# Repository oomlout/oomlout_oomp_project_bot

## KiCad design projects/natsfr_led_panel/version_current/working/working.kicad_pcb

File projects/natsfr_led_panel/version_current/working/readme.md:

# OOMP Project  
## Led_Panel  by natsfr  
  
oomp key: oomp_projects_flat_natsfr_led_panel  
(snippet of original readme)  

  full source readme at [readme_src.md](readme_src.md)  
  
source repo at: [https://github.com/natsfr/Led_Panel](https://github.com/natsfr/Led_Panel)  
## Board  

## Schematic  

[schematic pdf](working_schematic.pdf)  
## Images

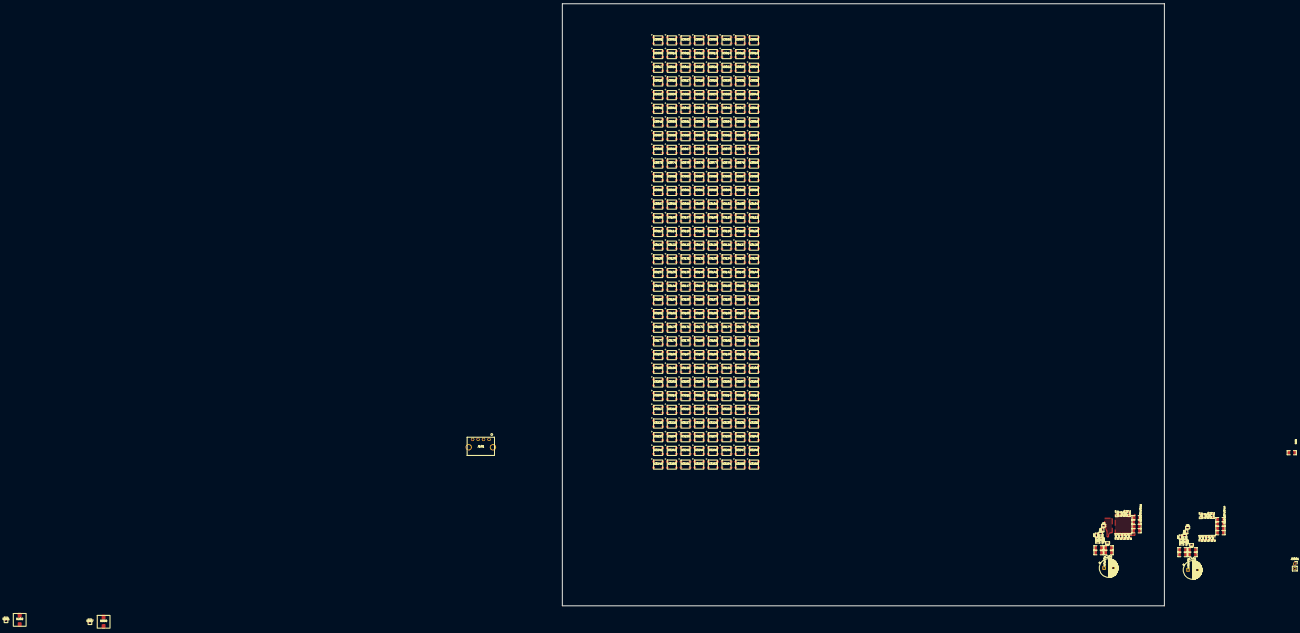
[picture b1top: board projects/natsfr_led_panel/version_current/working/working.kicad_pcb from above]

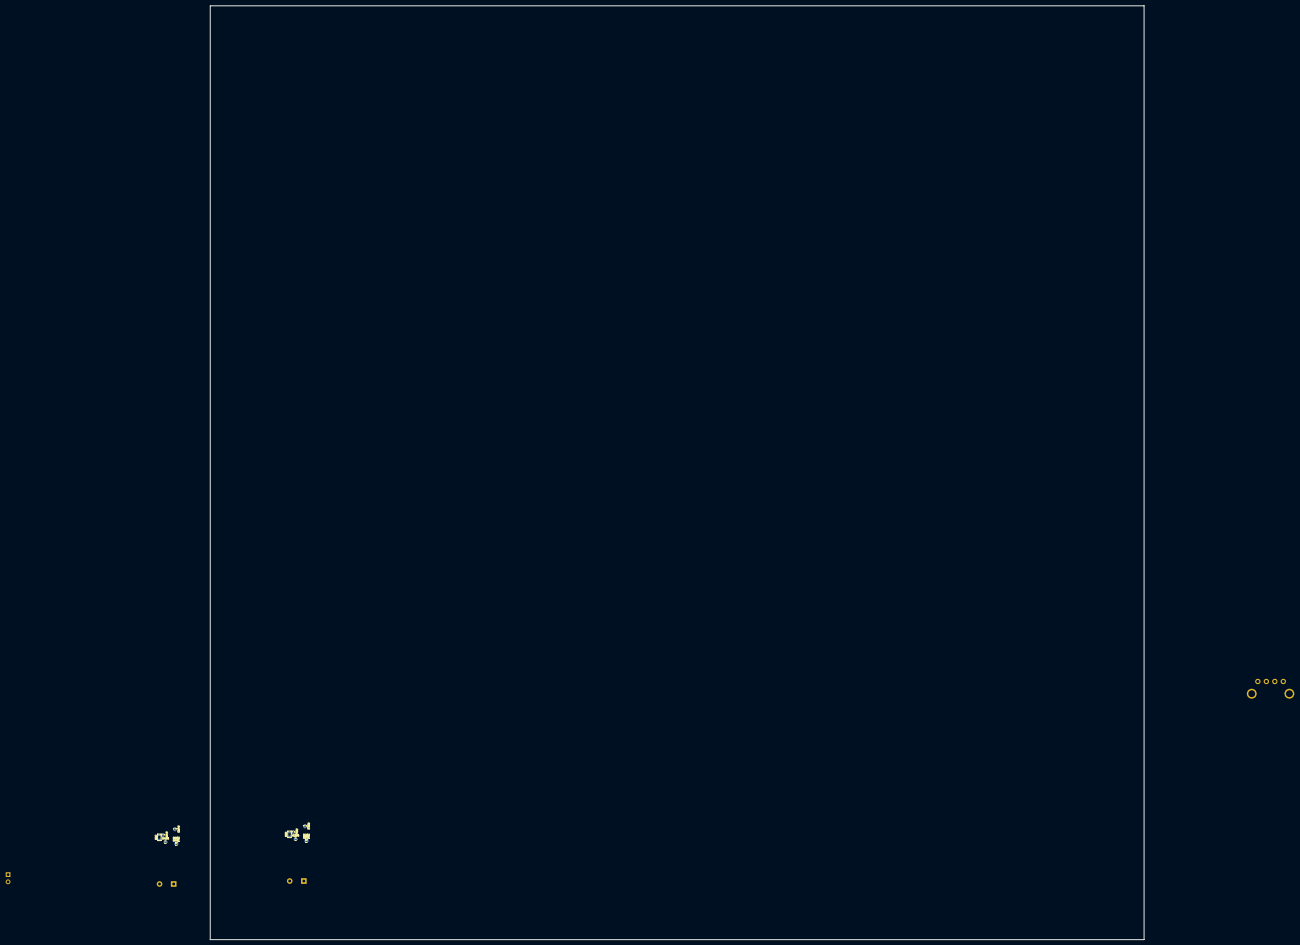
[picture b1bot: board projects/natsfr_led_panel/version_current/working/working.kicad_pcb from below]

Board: 4 copper layers, 330.0 x 330.0 mm, 331 parts (12 on the bottom side), 296 nets, no tracks yet.

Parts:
C201, C202, C203, C204, C402, C403, C404, C405: 10uF - 50V; SM1206
C205, C401: 100uF; CP_Radial_D10.0mm_P5.00mm
C206, C217, C218, C220, C406, C409, C419, C420: 100nF; SM0603
C207, C408: 220nF; SM0603
C208, C410: NC; SM0603
C209, C210, C211, C212, C213, C214, C215, C216, C411, C412, C413, C414, C415, C416, C417, C418: 10uF - 16V; SM0805
C219, C407: 1uF; SM0603
J101: 19V 5A Molex; MICROFIT_4POS_FEM_43650-0404
J3001: DEBUG_OUT; PinSocket_1x02_P2.54mm_Vertical
R101: RES_1206; SM1206
R201, R401: 1.5M; SM0402
R202, R212, R213, R402, R403, R404: NC; SM0402
R203, R409: 9.53k; SM0402
R204, R410: 43k; SM0402
R205, R405: 3.3; SM0603
R206, R207, R407, R408: NC; SM0603
R208, R209, R210, R211, R411, R412, R413, R414: 0; SM1206
R214, R406: 100k; SM0402
U201, U557: MP8759GD; MP8759_QFN12
U202, U558: IND_SMALL; WE-HCI_7x7x3.8mm
U3001, U3002, U3003, U3004, U3005, U3006, U3007, U3008, U3009, U3010, U3011, U3012, U3013, U3014, U3015, U3016, U3017, U3018, U3019, U3020, U3021, U3022, U3023, U3024, U3025, U3026, U3027, U3028, U3029, U3030, U3031, U3032, U3033, U3034, U3035, U3036, U3037, U3038, U3039, U3040, U3041, U3042, U3043, U3044, U3045, U3046, U3047, U3048, U3049, U3050, U3051, U3052, U3053, U3054, U3055, U3056, U3057, U3058, U3059, U3060, U3061, U3062, U3063, U3064, U3065, U3066, U3067, U3068, U3069, U3070, U3071, U3072, U3073, U3074, U3075, U3076, U3077, U3078, U3079, U3080, U3081, U3082, U3083, U3084, U3085, U3086, U3087, U3088, U3089, U3090, U3091, U3092, U3093, U3094, U3095, U3096, U3097, U3098, U3099, U3100, U3101, U3102, U3103, U3104, U3105, U3106, U3107, U3108, U3109, U3110, U3111, U3112, U3113, U3114, U3115, U3116, U3117, U3118, U3119, U3120, U3121, U3122, U3123, U3124, U3125, U3126, U3127, U3128, U3129, U3130, U3131, U3132, U3133, U3134, U3135, U3136, U3137, U3138, U3139, U3140, U3141, U3142, U3143, U3144, U3145, U3146, U3147, U3148, U3149, U3150, U3151, U3152, U3153, U3154, U3155, U3156, U3157, U3158, U3159, U3160, U3161, U3162, U3163, U3164, U3165, U3166, U3167, U3168, U3169, U3170, U3171, U3172, U3173, U3174, U3175, U3176, U3177, U3178, U3179, U3180, U3181, U3182, U3183, U3184, U3185, U3186, U3187, U3188, U3189, U3190, U3191, U3192, U3193, U3194, U3195, U3196, U3197, U3198, U3199, U3200, U3201, U3202, U3203, U3204, U3205, U3206, U3207, U3208, U3209, U3210, U3211, U3212, U3213, U3214, U3215, U3216, U3217, U3218, U3219, U3220, U3221, U3222, U3223, U3224, U3225, U3226, U3227, U3228, U3229, U3230, U3231, U3232, U3233, U3234, U3235, U3236, U3237, U3238, U3239, U3240, U3241, U3242, U3243, U3244, U3245, U3246, U3247, U3248, U3249, U3250, U3251, U3252, U3253, U3254, U3255, U3256: WS2812B; WS2812B_50x50

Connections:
/Lane 0/LANE_POWER: R101.2, U3001.1 (VDD), U3002.1 (VDD), U3003.1 (VDD), U3004.1 (VDD), U3005.1 (VDD), U3006.1 (VDD), U3007.1 (VDD), U3008.1 (VDD), U3009.1 (VDD), U3010.1 (VDD), U3011.1 (VDD), U3012.1 (VDD), U3013.1 (VDD), U3014.1 (VDD), U3015.1 (VDD), U3016.1 (VDD)
/Power Lane 0/19V: C201.2, C202.2, C203.2, C204.2, C205.2, C206.2, C401.2, C402.2, C403.2, C404.2, C405.2, C406.2, J101.3, J101.4, U201.1 (Vin), U557.1 (Vin)
/Power Lane 0/PG: R214.2, U201.3 (PG)
/Power Lane 0/POUT_SW: C208.2, C209.2, C210.2, C211.2, C212.2, C213.2, C214.2, C215.2, C216.2, C217.2, C218.2, C220.2, R204.1, R208.1, R209.1, R210.1, R211.1, U201.5 (Vout), U202.2
/Power Lane 0/POWER_OUT: R101.1, R208.2, R209.2, R210.2, R211.2
/Power Lane 0/SW: C207.2, R206.2, U201.7 (SW), U202.1
/Power Lane 1/PG: R406.2, U557.3 (PG)
/Power Lane 1/POUT_SW: C409.2, C410.2, C411.2, C412.2, C413.2, C414.2, C415.2, C416.2, C417.2, C418.2, C419.2, C420.2, R410.1, R411.1, R412.1, R413.1, R414.1, U557.5 (Vout), U558.2
/Power Lane 1/POWER_OUT: R411.2, R412.2, R413.2, R414.2
/Power Lane 1/SW: C408.2, R407.2, U557.7 (SW), U558.1
GND: C201.1, C202.1, C203.1, C204.1, C205.1, C206.1, C209.1, C210.1, C211.1, C212.1, C213.1, C214.1, C215.1, C216.1, C217.1, C218.1, C219.1, C220.1, C401.1, C402.1, C403.1, C404.1, C405.1, C406.1, C407.1, C409.1, C411.1, C412.1, C413.1, C414.1, C415.1, C416.1, C417.1, C418.1, C419.1, C420.1, J101.1, J101.2, J3001.1, R202.1, R203.1, R213.1, R402.1, R404.1, R409.1, U201.2 (PGND), U201.10 (AGND), U557.2 (PGND), U557.10 (AGND), U3001.3 (VSS), U3002.3 (VSS), U3003.3 (VSS), U3004.3 (VSS), U3005.3 (VSS), U3006.3 (VSS), U3007.3 (VSS), U3008.3 (VSS), U3009.3 (VSS), U3010.3 (VSS), U3011.3 (VSS), U3012.3 (VSS), U3013.3 (VSS), U3014.3 (VSS), U3015.3 (VSS), U3016.3 (VSS), U3017.3 (VSS), U3018.3 (VSS), U3019.3 (VSS), U3020.3 (VSS), U3021.3 (VSS), U3022.3 (VSS), U3023.3 (VSS), U3024.3 (VSS), U3025.3 (VSS), U3026.3 (VSS), U3027.3 (VSS), U3028.3 (VSS), U3029.3 (VSS), U3030.3 (VSS), U3031.3 (VSS), U3032.3 (VSS), U3033.3 (VSS), U3034.3 (VSS), U3035.3 (VSS), U3036.3 (VSS), U3037.3 (VSS), U3038.3 (VSS), U3039.3 (VSS), U3040.3 (VSS), U3041.3 (VSS), U3042.3 (VSS), U3043.3 (VSS), U3044.3 (VSS), U3045.3 (VSS), U3046.3 (VSS), U3047.3 (VSS), U3048.3 (VSS), U3049.3 (VSS), U3050.3 (VSS), U3051.3 (VSS), U3052.3 (VSS), U3053.3 (VSS), U3054.3 (VSS), U3055.3 (VSS), U3056.3 (VSS), U3057.3 (VSS), U3058.3 (VSS), U3059.3 (VSS), U3060.3 (VSS), U3061.3 (VSS), U3062.3 (VSS), U3063.3 (VSS), U3064.3 (VSS), U3065.3 (VSS), U3066.3 (VSS), U3067.3 (VSS), U3068.3 (VSS), U3069.3 (VSS), U3070.3 (VSS), U3071.3 (VSS), U3072.3 (VSS), U3073.3 (VSS), U3074.3 (VSS), U3075.3 (VSS), U3076.3 (VSS), U3077.3 (VSS), U3078.3 (VSS), U3079.3 (VSS), U3080.3 (VSS), U3081.3 (VSS), U3082.3 (VSS), U3083.3 (VSS), U3084.3 (VSS), U3085.3 (VSS), U3086.3 (VSS), U3087.3 (VSS), U3088.3 (VSS), U3089.3 (VSS), U3090.3 (VSS), U3091.3 (VSS), U3092.3 (VSS), U3093.3 (VSS), U3094.3 (VSS), U3095.3 (VSS), U3096.3 (VSS), U3097.3 (VSS), U3098.3 (VSS), U3099.3 (VSS), U3100.3 (VSS), U3101.3 (VSS), U3102.3 (VSS), U3103.3 (VSS), U3104.3 (VSS), U3105.3 (VSS), U3106.3 (VSS), U3107.3 (VSS), U3108.3 (VSS), U3109.3 (VSS), U3110.3 (VSS), U3111.3 (VSS), U3112.3 (VSS), U3113.3 (VSS), U3114.3 (VSS), U3115.3 (VSS), U3116.3 (VSS), U3117.3 (VSS), U3118.3 (VSS), U3119.3 (VSS), U3120.3 (VSS), U3121.3 (VSS), U3122.3 (VSS), U3123.3 (VSS), U3124.3 (VSS), U3125.3 (VSS), U3126.3 (VSS), U3127.3 (VSS), U3128.3 (VSS), U3129.3 (VSS), U3130.3 (VSS), U3131.3 (VSS), U3132.3 (VSS), U3133.3 (VSS), U3134.3 (VSS), U3135.3 (VSS), U3136.3 (VSS), U3137.3 (VSS), U3138.3 (VSS), U3139.3 (VSS), U3140.3 (VSS), U3141.3 (VSS), U3142.3 (VSS), U3143.3 (VSS), U3144.3 (VSS), U3145.3 (VSS), U3146.3 (VSS), U3147.3 (VSS), U3148.3 (VSS), U3149.3 (VSS), U3150.3 (VSS), U3151.3 (VSS), U3152.3 (VSS), U3153.3 (VSS), U3154.3 (VSS), U3155.3 (VSS), U3156.3 (VSS), U3157.3 (VSS), U3158.3 (VSS), U3159.3 (VSS), U3160.3 (VSS), U3161.3 (VSS), U3162.3 (VSS), U3163.3 (VSS), U3164.3 (VSS), U3165.3 (VSS), U3166.3 (VSS), U3167.3 (VSS), U3168.3 (VSS), U3169.3 (VSS), U3170.3 (VSS), U3171.3 (VSS), U3172.3 (VSS), U3173.3 (VSS), U3174.3 (VSS), U3175.3 (VSS), U3176.3 (VSS), U3177.3 (VSS), U3178.3 (VSS), U3179.3 (VSS), U3180.3 (VSS), U3181.3 (VSS), U3182.3 (VSS), U3183.3 (VSS), U3184.3 (VSS), U3185.3 (VSS), U3186.3 (VSS), U3187.3 (VSS), U3188.3 (VSS), U3189.3 (VSS), U3190.3 (VSS), U3191.3 (VSS), U3192.3 (VSS), U3193.3 (VSS), U3194.3 (VSS), U3195.3 (VSS), U3196.3 (VSS), U3197.3 (VSS), U3198.3 (VSS), U3199.3 (VSS), U3200.3 (VSS), U3201.3 (VSS), U3202.3 (VSS), U3203.3 (VSS), U3204.3 (VSS), U3205.3 (VSS), U3206.3 (VSS), U3207.3 (VSS), U3208.3 (VSS), U3209.3 (VSS), U3210.3 (VSS), U3211.3 (VSS), U3212.3 (VSS), U3213.3 (VSS), U3214.3 (VSS), U3215.3 (VSS), U3216.3 (VSS), U3217.3 (VSS), U3218.3 (VSS), U3219.3 (VSS), U3220.3 (VSS), U3221.3 (VSS), U3222.3 (VSS), U3223.3 (VSS), U3224.3 (VSS), U3225.3 (VSS), U3226.3 (VSS), U3227.3 (VSS), U3228.3 (VSS), U3229.3 (VSS), U3230.3 (VSS), U3231.3 (VSS), U3232.3 (VSS), U3233.3 (VSS), U3234.3 (VSS), U3235.3 (VSS), U3236.3 (VSS), U3237.3 (VSS), U3238.3 (VSS), U3239.3 (VSS), U3240.3 (VSS), U3241.3 (VSS), U3242.3 (VSS), U3243.3 (VSS), U3244.3 (VSS), U3245.3 (VSS), U3246.3 (VSS), U3247.3 (VSS), U3248.3 (VSS), U3249.3 (VSS), U3250.3 (VSS), U3251.3 (VSS), U3252.3 (VSS), U3253.3 (VSS), U3254.3 (VSS), U3255.3 (VSS), U3256.3 (VSS)
unnamed: C207.1, R205.2
unnamed: C208.1, R206.1, R207.2
unnamed: C407.2, R403.1, R406.1, U557.9 (Vcc)
unnamed: C408.1, R405.2
unnamed: C410.1, R407.1, R408.2
unnamed: J3001.2, U3256.2 (DOUT)
unnamed: R201.2, R202.2, U201.12 (EN)
unnamed: R203.2, R204.2, R207.1, U201.11 (FB)
unnamed: R205.1, U201.8 (BST)
unnamed: R401.2, R402.2, U557.12 (EN)
unnamed: R403.2, R404.2, U557.6 (MODE)
unnamed: R405.1, U557.8 (BST)
unnamed: R408.1, R409.2, R410.2, U557.11 (FB)
unnamed: R212.2, R213.2
unnamed: C219.2, R212.1, R214.1
unnamed: U3001.2 (DOUT), U3002.4 (DIN)
unnamed: U3002.2 (DOUT), U3003.4 (DIN)
unnamed: U3003.2 (DOUT), U3004.4 (DIN)
unnamed: U3004.2 (DOUT), U3005.4 (DIN)
unnamed: U3005.2 (DOUT), U3006.4 (DIN)
unnamed: U3006.2 (DOUT), U3007.4 (DIN)
unnamed: U3007.2 (DOUT), U3008.4 (DIN)
unnamed: U3008.2 (DOUT), U3009.4 (DIN)
unnamed: U3009.2 (DOUT), U3010.4 (DIN)
unnamed: U3010.2 (DOUT), U3011.4 (DIN)
unnamed: U3011.2 (DOUT), U3012.4 (DIN)
unnamed: U3012.2 (DOUT), U3013.4 (DIN)
unnamed: U3013.2 (DOUT), U3014.4 (DIN)
unnamed: U3014.2 (DOUT), U3015.4 (DIN)
unnamed: U3015.2 (DOUT), U3016.4 (DIN)
unnamed: U3016.2 (DOUT), U3017.4 (DIN)
unnamed: U3017.1 (VDD), U3018.1 (VDD), U3019.1 (VDD), U3020.1 (VDD), U3021.1 (VDD), U3022.1 (VDD), U3023.1 (VDD), U3024.1 (VDD), U3025.1 (VDD), U3026.1 (VDD), U3027.1 (VDD), U3028.1 (VDD), U3029.1 (VDD), U3030.1 (VDD), U3031.1 (VDD), U3032.1 (VDD)
unnamed: U3017.2 (DOUT), U3018.4 (DIN)
unnamed: U3018.2 (DOUT), U3019.4 (DIN)
unnamed: U3019.2 (DOUT), U3020.4 (DIN)
unnamed: U3020.2 (DOUT), U3021.4 (DIN)
unnamed: U3021.2 (DOUT), U3022.4 (DIN)
unnamed: U3022.2 (DOUT), U3023.4 (DIN)
unnamed: U3023.2 (DOUT), U3024.4 (DIN)
unnamed: U3024.2 (DOUT), U3025.4 (DIN)
unnamed: U3025.2 (DOUT), U3026.4 (DIN)
unnamed: U3026.2 (DOUT), U3027.4 (DIN)
unnamed: U3027.2 (DOUT), U3028.4 (DIN)
unnamed: U3028.2 (DOUT), U3029.4 (DIN)
unnamed: U3029.2 (DOUT), U3030.4 (DIN)
unnamed: U3030.2 (DOUT), U3031.4 (DIN)
unnamed: U3031.2 (DOUT), U3032.4 (DIN)
unnamed: U3032.2 (DOUT), U3033.4 (DIN)
unnamed: U3033.1 (VDD), U3034.1 (VDD), U3035.1 (VDD), U3036.1 (VDD), U3037.1 (VDD), U3038.1 (VDD), U3039.1 (VDD), U3040.1 (VDD), U3041.1 (VDD), U3042.1 (VDD), U3043.1 (VDD), U3044.1 (VDD), U3045.1 (VDD), U3046.1 (VDD), U3047.1 (VDD), U3048.1 (VDD)
unnamed: U3033.2 (DOUT), U3034.4 (DIN)
unnamed: U3034.2 (DOUT), U3035.4 (DIN)
unnamed: U3035.2 (DOUT), U3036.4 (DIN)
unnamed: U3036.2 (DOUT), U3037.4 (DIN)
unnamed: U3037.2 (DOUT), U3038.4 (DIN)
unnamed: U3038.2 (DOUT), U3039.4 (DIN)
unnamed: U3039.2 (DOUT), U3040.4 (DIN)
unnamed: U3040.2 (DOUT), U3041.4 (DIN)
unnamed: U3041.2 (DOUT), U3042.4 (DIN)
unnamed: U3042.2 (DOUT), U3043.4 (DIN)
unnamed: U3043.2 (DOUT), U3044.4 (DIN)
unnamed: U3044.2 (DOUT), U3045.4 (DIN)
unnamed: U3045.2 (DOUT), U3046.4 (DIN)
unnamed: U3046.2 (DOUT), U3047.4 (DIN)
unnamed: U3047.2 (DOUT), U3048.4 (DIN)
unnamed: U3048.2 (DOUT), U3049.4 (DIN)
unnamed: U3049.1 (VDD), U3050.1 (VDD), U3051.1 (VDD), U3052.1 (VDD), U3053.1 (VDD), U3054.1 (VDD), U3055.1 (VDD), U3056.1 (VDD), U3057.1 (VDD), U3058.1 (VDD), U3059.1 (VDD), U3060.1 (VDD), U3061.1 (VDD), U3062.1 (VDD), U3063.1 (VDD), U3064.1 (VDD)
unnamed: U3049.2 (DOUT), U3050.4 (DIN)
unnamed: U3050.2 (DOUT), U3051.4 (DIN)
unnamed: U3051.2 (DOUT), U3052.4 (DIN)
unnamed: U3052.2 (DOUT), U3053.4 (DIN)
unnamed: U3053.2 (DOUT), U3054.4 (DIN)
unnamed: U3054.2 (DOUT), U3055.4 (DIN)
unnamed: U3055.2 (DOUT), U3056.4 (DIN)
unnamed: U3056.2 (DOUT), U3057.4 (DIN)
unnamed: U3057.2 (DOUT), U3058.4 (DIN)
unnamed: U3058.2 (DOUT), U3059.4 (DIN)
unnamed: U3059.2 (DOUT), U3060.4 (DIN)
unnamed: U3060.2 (DOUT), U3061.4 (DIN)
unnamed: U3061.2 (DOUT), U3062.4 (DIN)
unnamed: U3062.2 (DOUT), U3063.4 (DIN)
unnamed: U3063.2 (DOUT), U3064.4 (DIN)
unnamed: U3064.2 (DOUT), U3065.4 (DIN)
unnamed: U3065.1 (VDD), U3066.1 (VDD), U3067.1 (VDD), U3068.1 (VDD), U3069.1 (VDD), U3070.1 (VDD), U3071.1 (VDD), U3072.1 (VDD), U3073.1 (VDD), U3074.1 (VDD), U3075.1 (VDD), U3076.1 (VDD), U3077.1 (VDD), U3078.1 (VDD), U3079.1 (VDD), U3080.1 (VDD)
unnamed: U3065.2 (DOUT), U3066.4 (DIN)
unnamed: U3066.2 (DOUT), U3067.4 (DIN)
unnamed: U3067.2 (DOUT), U3068.4 (DIN)
unnamed: U3068.2 (DOUT), U3069.4 (DIN)
unnamed: U3069.2 (DOUT), U3070.4 (DIN)
unnamed: U3070.2 (DOUT), U3071.4 (DIN)
unnamed: U3071.2 (DOUT), U3072.4 (DIN)
unnamed: U3072.2 (DOUT), U3073.4 (DIN)
unnamed: U3073.2 (DOUT), U3074.4 (DIN)
unnamed: U3074.2 (DOUT), U3075.4 (DIN)
unnamed: U3075.2 (DOUT), U3076.4 (DIN)
unnamed: U3076.2 (DOUT), U3077.4 (DIN)
unnamed: U3077.2 (DOUT), U3078.4 (DIN)
unnamed: U3078.2 (DOUT), U3079.4 (DIN)
unnamed: U3079.2 (DOUT), U3080.4 (DIN)
unnamed: U3080.2 (DOUT), U3081.4 (DIN)
unnamed: U3081.1 (VDD), U3082.1 (VDD), U3083.1 (VDD), U3084.1 (VDD), U3085.1 (VDD), U3086.1 (VDD), U3087.1 (VDD), U3088.1 (VDD), U3089.1 (VDD), U3090.1 (VDD), U3091.1 (VDD), U3092.1 (VDD), U3093.1 (VDD), U3094.1 (VDD), U3095.1 (VDD), U3096.1 (VDD)
unnamed: U3081.2 (DOUT), U3082.4 (DIN)
unnamed: U3082.2 (DOUT), U3083.4 (DIN)
unnamed: U3083.2 (DOUT), U3084.4 (DIN)
unnamed: U3084.2 (DOUT), U3085.4 (DIN)
unnamed: U3085.2 (DOUT), U3086.4 (DIN)
unnamed: U3086.2 (DOUT), U3087.4 (DIN)
unnamed: U3087.2 (DOUT), U3088.4 (DIN)
unnamed: U3088.2 (DOUT), U3089.4 (DIN)
unnamed: U3089.2 (DOUT), U3090.4 (DIN)
unnamed: U3090.2 (DOUT), U3091.4 (DIN)
unnamed: U3091.2 (DOUT), U3092.4 (DIN)
unnamed: U3092.2 (DOUT), U3093.4 (DIN)
unnamed: U3093.2 (DOUT), U3094.4 (DIN)
unnamed: U3094.2 (DOUT), U3095.4 (DIN)
unnamed: U3095.2 (DOUT), U3096.4 (DIN)
unnamed: U3096.2 (DOUT), U3097.4 (DIN)
unnamed: U3097.1 (VDD), U3098.1 (VDD), U3099.1 (VDD), U3100.1 (VDD), U3101.1 (VDD), U3102.1 (VDD), U3103.1 (VDD), U3104.1 (VDD), U3105.1 (VDD), U3106.1 (VDD), U3107.1 (VDD), U3108.1 (VDD), U3109.1 (VDD), U3110.1 (VDD), U3111.1 (VDD), U3112.1 (VDD)
unnamed: U3097.2 (DOUT), U3098.4 (DIN)
unnamed: U3098.2 (DOUT), U3099.4 (DIN)
unnamed: U3099.2 (DOUT), U3100.4 (DIN)
unnamed: U3100.2 (DOUT), U3101.4 (DIN)
unnamed: U3101.2 (DOUT), U3102.4 (DIN)
unnamed: U3102.2 (DOUT), U3103.4 (DIN)
unnamed: U3103.2 (DOUT), U3104.4 (DIN)
unnamed: U3104.2 (DOUT), U3105.4 (DIN)
unnamed: U3105.2 (DOUT), U3106.4 (DIN)
unnamed: U3106.2 (DOUT), U3107.4 (DIN)
unnamed: U3107.2 (DOUT), U3108.4 (DIN)
unnamed: U3108.2 (DOUT), U3109.4 (DIN)
unnamed: U3109.2 (DOUT), U3110.4 (DIN)
unnamed: U3110.2 (DOUT), U3111.4 (DIN)
unnamed: U3111.2 (DOUT), U3112.4 (DIN)
unnamed: U3112.2 (DOUT), U3113.4 (DIN)
unnamed: U3113.1 (VDD), U3114.1 (VDD), U3115.1 (VDD), U3116.1 (VDD), U3117.1 (VDD), U3118.1 (VDD), U3119.1 (VDD), U3120.1 (VDD), U3121.1 (VDD), U3122.1 (VDD), U3123.1 (VDD), U3124.1 (VDD), U3125.1 (VDD), U3126.1 (VDD), U3127.1 (VDD), U3128.1 (VDD)
unnamed: U3113.2 (DOUT), U3114.4 (DIN)
unnamed: U3114.2 (DOUT), U3115.4 (DIN)
unnamed: U3115.2 (DOUT), U3116.4 (DIN)
unnamed: U3116.2 (DOUT), U3117.4 (DIN)
unnamed: U3117.2 (DOUT), U3118.4 (DIN)
unnamed: U3118.2 (DOUT), U3119.4 (DIN)
unnamed: U3119.2 (DOUT), U3120.4 (DIN)
unnamed: U3120.2 (DOUT), U3121.4 (DIN)
unnamed: U3121.2 (DOUT), U3122.4 (DIN)
unnamed: U3122.2 (DOUT), U3123.4 (DIN)
unnamed: U3123.2 (DOUT), U3124.4 (DIN)
unnamed: U3124.2 (DOUT), U3125.4 (DIN)
unnamed: U3125.2 (DOUT), U3126.4 (DIN)
unnamed: U3126.2 (DOUT), U3127.4 (DIN)
unnamed: U3127.2 (DOUT), U3128.4 (DIN)
unnamed: U3128.2 (DOUT), U3129.4 (DIN)
unnamed: U3129.1 (VDD), U3130.1 (VDD), U3131.1 (VDD), U3132.1 (VDD), U3133.1 (VDD), U3134.1 (VDD), U3135.1 (VDD), U3136.1 (VDD), U3137.1 (VDD), U3138.1 (VDD), U3139.1 (VDD), U3140.1 (VDD), U3141.1 (VDD), U3142.1 (VDD), U3143.1 (VDD), U3144.1 (VDD)
unnamed: U3129.2 (DOUT), U3130.4 (DIN)
unnamed: U3130.2 (DOUT), U3131.4 (DIN)
unnamed: U3131.2 (DOUT), U3132.4 (DIN)
unnamed: U3132.2 (DOUT), U3133.4 (DIN)
unnamed: U3133.2 (DOUT), U3134.4 (DIN)
unnamed: U3134.2 (DOUT), U3135.4 (DIN)
unnamed: U3135.2 (DOUT), U3136.4 (DIN)
unnamed: U3136.2 (DOUT), U3137.4 (DIN)
unnamed: U3137.2 (DOUT), U3138.4 (DIN)
unnamed: U3138.2 (DOUT), U3139.4 (DIN)
unnamed: U3139.2 (DOUT), U3140.4 (DIN)
unnamed: U3140.2 (DOUT), U3141.4 (DIN)
unnamed: U3141.2 (DOUT), U3142.4 (DIN)
unnamed: U3142.2 (DOUT), U3143.4 (DIN)
unnamed: U3143.2 (DOUT), U3144.4 (DIN)
unnamed: U3144.2 (DOUT), U3145.4 (DIN)
unnamed: U3145.1 (VDD), U3146.1 (VDD), U3147.1 (VDD), U3148.1 (VDD), U3149.1 (VDD), U3150.1 (VDD), U3151.1 (VDD), U3152.1 (VDD), U3153.1 (VDD), U3154.1 (VDD), U3155.1 (VDD), U3156.1 (VDD), U3157.1 (VDD), U3158.1 (VDD), U3159.1 (VDD), U3160.1 (VDD)
unnamed: U3145.2 (DOUT), U3146.4 (DIN)
unnamed: U3146.2 (DOUT), U3147.4 (DIN)
unnamed: U3147.2 (DOUT), U3148.4 (DIN)
unnamed: U3148.2 (DOUT), U3149.4 (DIN)
unnamed: U3149.2 (DOUT), U3150.4 (DIN)
unnamed: U3150.2 (DOUT), U3151.4 (DIN)
unnamed: U3151.2 (DOUT), U3152.4 (DIN)
unnamed: U3152.2 (DOUT), U3153.4 (DIN)
unnamed: U3153.2 (DOUT), U3154.4 (DIN)
unnamed: U3154.2 (DOUT), U3155.4 (DIN)
unnamed: U3155.2 (DOUT), U3156.4 (DIN)
unnamed: U3156.2 (DOUT), U3157.4 (DIN)
unnamed: U3157.2 (DOUT), U3158.4 (DIN)
unnamed: U3158.2 (DOUT), U3159.4 (DIN)
unnamed: U3159.2 (DOUT), U3160.4 (DIN)
unnamed: U3160.2 (DOUT), U3161.4 (DIN)
unnamed: U3161.1 (VDD), U3162.1 (VDD), U3163.1 (VDD), U3164.1 (VDD), U3165.1 (VDD), U3166.1 (VDD), U3167.1 (VDD), U3168.1 (VDD), U3169.1 (VDD), U3170.1 (VDD), U3171.1 (VDD), U3172.1 (VDD), U3173.1 (VDD), U3174.1 (VDD), U3175.1 (VDD), U3176.1 (VDD)
unnamed: U3161.2 (DOUT), U3162.4 (DIN)
unnamed: U3162.2 (DOUT), U3163.4 (DIN)
unnamed: U3163.2 (DOUT), U3164.4 (DIN)
unnamed: U3164.2 (DOUT), U3165.4 (DIN)
unnamed: U3165.2 (DOUT), U3166.4 (DIN)
unnamed: U3166.2 (DOUT), U3167.4 (DIN)
unnamed: U3167.2 (DOUT), U3168.4 (DIN)
unnamed: U3168.2 (DOUT), U3169.4 (DIN)
unnamed: U3169.2 (DOUT), U3170.4 (DIN)
unnamed: U3170.2 (DOUT), U3171.4 (DIN)
unnamed: U3171.2 (DOUT), U3172.4 (DIN)
unnamed: U3172.2 (DOUT), U3173.4 (DIN)
unnamed: U3173.2 (DOUT), U3174.4 (DIN)
unnamed: U3174.2 (DOUT), U3175.4 (DIN)
unnamed: U3175.2 (DOUT), U3176.4 (DIN)
unnamed: U3176.2 (DOUT), U3177.4 (DIN)
unnamed: U3177.1 (VDD), U3178.1 (VDD), U3179.1 (VDD), U3180.1 (VDD), U3181.1 (VDD), U3182.1 (VDD), U3183.1 (VDD), U3184.1 (VDD), U3185.1 (VDD), U3186.1 (VDD), U3187.1 (VDD), U3188.1 (VDD), U3189.1 (VDD), U3190.1 (VDD), U3191.1 (VDD), U3192.1 (VDD)
unnamed: U3177.2 (DOUT), U3178.4 (DIN)
unnamed: U3178.2 (DOUT), U3179.4 (DIN)
unnamed: U3179.2 (DOUT), U3180.4 (DIN)
unnamed: U3180.2 (DOUT), U3181.4 (DIN)
unnamed: U3181.2 (DOUT), U3182.4 (DIN)
unnamed: U3182.2 (DOUT), U3183.4 (DIN)
unnamed: U3183.2 (DOUT), U3184.4 (DIN)
unnamed: U3184.2 (DOUT), U3185.4 (DIN)
unnamed: U3185.2 (DOUT), U3186.4 (DIN)
unnamed: U3186.2 (DOUT), U3187.4 (DIN)
unnamed: U3187.2 (DOUT), U3188.4 (DIN)
unnamed: U3188.2 (DOUT), U3189.4 (DIN)
unnamed: U3189.2 (DOUT), U3190.4 (DIN)
unnamed: U3190.2 (DOUT), U3191.4 (DIN)
unnamed: U3191.2 (DOUT), U3192.4 (DIN)
unnamed: U3192.2 (DOUT), U3193.4 (DIN)
unnamed: U3193.1 (VDD), U3194.1 (VDD), U3195.1 (VDD), U3196.1 (VDD), U3197.1 (VDD), U3198.1 (VDD), U3199.1 (VDD), U3200.1 (VDD), U3201.1 (VDD), U3202.1 (VDD), U3203.1 (VDD), U3204.1 (VDD), U3205.1 (VDD), U3206.1 (VDD), U3207.1 (VDD), U3208.1 (VDD)
unnamed: U3193.2 (DOUT), U3194.4 (DIN)
unnamed: U3194.2 (DOUT), U3195.4 (DIN)
unnamed: U3195.2 (DOUT), U3196.4 (DIN)
unnamed: U3196.2 (DOUT), U3197.4 (DIN)
unnamed: U3197.2 (DOUT), U3198.4 (DIN)
unnamed: U3198.2 (DOUT), U3199.4 (DIN)
unnamed: U3199.2 (DOUT), U3200.4 (DIN)
unnamed: U3200.2 (DOUT), U3201.4 (DIN)
unnamed: U3201.2 (DOUT), U3202.4 (DIN)
unnamed: U3202.2 (DOUT), U3203.4 (DIN)
unnamed: U3203.2 (DOUT), U3204.4 (DIN)
unnamed: U3204.2 (DOUT), U3205.4 (DIN)
unnamed: U3205.2 (DOUT), U3206.4 (DIN)
unnamed: U3206.2 (DOUT), U3207.4 (DIN)
unnamed: U3207.2 (DOUT), U3208.4 (DIN)
unnamed: U3208.2 (DOUT), U3209.4 (DIN)
unnamed: U3209.1 (VDD), U3210.1 (VDD), U3211.1 (VDD), U3212.1 (VDD), U3213.1 (VDD), U3214.1 (VDD), U3215.1 (VDD), U3216.1 (VDD), U3217.1 (VDD), U3218.1 (VDD), U3219.1 (VDD), U3220.1 (VDD), U3221.1 (VDD), U3222.1 (VDD), U3223.1 (VDD), U3224.1 (VDD)
unnamed: U3209.2 (DOUT), U3210.4 (DIN)
unnamed: U3210.2 (DOUT), U3211.4 (DIN)
unnamed: U3211.2 (DOUT), U3212.4 (DIN)
unnamed: U3212.2 (DOUT), U3213.4 (DIN)
unnamed: U3213.2 (DOUT), U3214.4 (DIN)
unnamed: U3214.2 (DOUT), U3215.4 (DIN)
unnamed: U3215.2 (DOUT), U3216.4 (DIN)
unnamed: U3216.2 (DOUT), U3217.4 (DIN)
unnamed: U3217.2 (DOUT), U3218.4 (DIN)
unnamed: U3218.2 (DOUT), U3219.4 (DIN)
unnamed: U3219.2 (DOUT), U3220.4 (DIN)
unnamed: U3220.2 (DOUT), U3221.4 (DIN)
unnamed: U3221.2 (DOUT), U3222.4 (DIN)
unnamed: U3222.2 (DOUT), U3223.4 (DIN)
unnamed: U3223.2 (DOUT), U3224.4 (DIN)
unnamed: U3224.2 (DOUT), U3225.4 (DIN)
unnamed: U3225.1 (VDD), U3226.1 (VDD), U3227.1 (VDD), U3228.1 (VDD), U3229.1 (VDD), U3230.1 (VDD), U3231.1 (VDD), U3232.1 (VDD), U3233.1 (VDD), U3234.1 (VDD), U3235.1 (VDD), U3236.1 (VDD), U3237.1 (VDD), U3238.1 (VDD), U3239.1 (VDD), U3240.1 (VDD)
unnamed: U3225.2 (DOUT), U3226.4 (DIN)
unnamed: U3226.2 (DOUT), U3227.4 (DIN)
unnamed: U3227.2 (DOUT), U3228.4 (DIN)
unnamed: U3228.2 (DOUT), U3229.4 (DIN)
unnamed: U3229.2 (DOUT), U3230.4 (DIN)
unnamed: U3230.2 (DOUT), U3231.4 (DIN)
unnamed: U3231.2 (DOUT), U3232.4 (DIN)
unnamed: U3232.2 (DOUT), U3233.4 (DIN)
unnamed: U3233.2 (DOUT), U3234.4 (DIN)
unnamed: U3234.2 (DOUT), U3235.4 (DIN)
unnamed: U3235.2 (DOUT), U3236.4 (DIN)
unnamed: U3236.2 (DOUT), U3237.4 (DIN)
unnamed: U3237.2 (DOUT), U3238.4 (DIN)
unnamed: U3238.2 (DOUT), U3239.4 (DIN)
unnamed: U3239.2 (DOUT), U3240.4 (DIN)
unnamed: U3240.2 (DOUT), U3241.4 (DIN)
unnamed: U3241.1 (VDD), U3242.1 (VDD), U3243.1 (VDD), U3244.1 (VDD), U3245.1 (VDD), U3246.1 (VDD), U3247.1 (VDD), U3248.1 (VDD), U3249.1 (VDD), U3250.1 (VDD), U3251.1 (VDD), U3252.1 (VDD), U3253.1 (VDD), U3254.1 (VDD), U3255.1 (VDD), U3256.1 (VDD)
unnamed: U3241.2 (DOUT), U3242.4 (DIN)
unnamed: U3242.2 (DOUT), U3243.4 (DIN)
unnamed: U3243.2 (DOUT), U3244.4 (DIN)
unnamed: U3244.2 (DOUT), U3245.4 (DIN)
unnamed: U3245.2 (DOUT), U3246.4 (DIN)
unnamed: U3246.2 (DOUT), U3247.4 (DIN)
unnamed: U3247.2 (DOUT), U3248.4 (DIN)
unnamed: U3248.2 (DOUT), U3249.4 (DIN)
unnamed: U3249.2 (DOUT), U3250.4 (DIN)
unnamed: U3250.2 (DOUT), U3251.4 (DIN)
unnamed: U3251.2 (DOUT), U3252.4 (DIN)
unnamed: U3252.2 (DOUT), U3253.4 (DIN)
unnamed: U3253.2 (DOUT), U3254.4 (DIN)
unnamed: U3254.2 (DOUT), U3255.4 (DIN)
unnamed: U3255.2 (DOUT), U3256.4 (DIN)

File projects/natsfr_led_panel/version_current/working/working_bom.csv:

"Id";"Designator";"Footprint";"Quantity";"Designation";"Supplier and ref";
1;"U3190,U3021,U3006,U3116,U3152,U3128,U3018,U3009,U3153,U3108,U3104,U3121,U3012,U3019,U3174,U3240,U3203,U3100,U3227,U3050,U3173,U3131,U3196,U3124,U3216,U3177,U3213,U3045,U3148,U3239,U3094,U3047,U3206,U3059,U3243,U3080,U3034,U3132,U3038,U3133,U3251,U3207,U3005,U3046,U3118,U3114,U3220,U3180,U3060,U3237,U3066,U3120,U3141,U3219,U3169,U3146,U3110,U3056,U3074,U3078,U3244,U3016,U3139,U3168,U3043,U3125,U3130,U3225,U3145,U3063,U3083,U3061,U3049,U3075,U3164,U3040,U3252,U3184,U3037,U3231,U3106,U3086,U3092,U3102,U3033,U3041,U3127,U3082,U3071,U3233,U3214,U3003,U3023,U3113,U3188,U3068,U3167,U3053,U3101,U3248,U3256,U3088,U3115,U3224,U3204,U3247,U3181,U3150,U3228,U3085,U3123,U3254,U3064,U3221,U3039,U3185,U3022,U3044,U3151,U3200,U3025,U3242,U3027,U3057,U3084,U3195,U3035,U3098,U3212,U3162,U3187,U3189,U3052,U3129,U3234,U3076,U3208,U3081,U3042,U3126,U3165,U3030,U3178,U3157,U3007,U3136,U3072,U3198,U3194,U3065,U3107,U3008,U3017,U3001,U3183,U3144,U3182,U3029,U3036,U3010,U3253,U3209,U3143,U3069,U3093,U3091,U3154,U3062,U3149,U3156,U3122,U3011,U3255,U3096,U3058,U3232,U3241,U3077,U3199,U3215,U3229,U3170,U3201,U3014,U3111,U3134,U3155,U3249,U3230,U3211,U3097,U3015,U3166,U3238,U3024,U3138,U3158,U3202,U3135,U3103,U3179,U3055,U3175,U3226,U3137,U3176,U3147,U3191,U3159,U3119,U3109,U3105,U3032,U3020,U3048,U3223,U3067,U3217,U3051,U3160,U3117,U3192,U3245,U3073,U3161,U3142,U3171,U3087,U3197,U3002,U3079,U3140,U3205,U3218,U3004,U3089,U3112,U3054,U3250,U3246,U3090,U3099,U3172,U3031,U3235,U3163,U3026,U3236,U3222,U3013,U3070,U3210,U3186,U3028,U3095,U3193";"WS2812B_50x50";256;"WS2812B";;;
2;"R101";"SM1206";1;"RES_1206";;;
3;"C201,C202,C403,C402,C204,C404,C203,C405";"SM1206";8;"10uF - 50V";;;
4;"R210,R414,R208,R413,R411,R209,R412,R211";"SM1206";8;"0";;;
5;"C219,C407";"SM0603";2;"1uF";;;
6;"R204,R410";"SM0402";2;"43k";;;
7;"C415,C417,C210,C214,C216,C416,C414,C411,C211,C413,C212,C418,C412,C213,C209,C215";"SM0805";16;"10uF - 16V";;;
8;"C206,C420,C217,C218,C406,C419,C220,C409";"SM0603";8;"100nF";;;
9;"C401,C205";"CP_Radial_D10.0mm_P5.00mm";2;"100uF";;;
10;"R409,R203";"SM0402";2;"9.53k";;;
11;"R206,R407,R408,R207,C208,C410";"SM0603";6;"NC";;;
12;"U201,U557";"MP8759_QFN12";2;"MP8759GD";;;
13;"C207,C408";"SM0603";2;"220nF";;;
14;"R205,R405";"SM0603";2;"3.3";;;
15;"U558,U202";"WE-HCI_7x7x3.8mm";2;"IND_SMALL";;;
16;"J101";"MICROFIT_4POS_FEM_43650-0404";1;"19V 5A Molex";;;
17;"J3001";"PinSocket_1x02_P2.54mm_Vertical";1;"DEBUG_OUT";;;
18;"R214,R406";"SM0402";2;"100k";;;
19;"R403,R213,R212,R404,R402,R202";"SM0402";6;"NC";;;
20;"R401,R201";"SM0402";2;"1.5M";;;

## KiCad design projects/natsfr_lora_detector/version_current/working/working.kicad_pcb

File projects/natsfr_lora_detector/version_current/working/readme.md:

# Lora_detector by natsfr  
This is a harvested standardized copy of a project from github.  
The original project can be found at:  
https://github.com/natsfr/Lora_detector  
Please consult that link for additional, details, files, and license information.  
Note: It was auto harvested and if the original repo had more than one board file or anything out of the ordinary the files here are likely not representative.

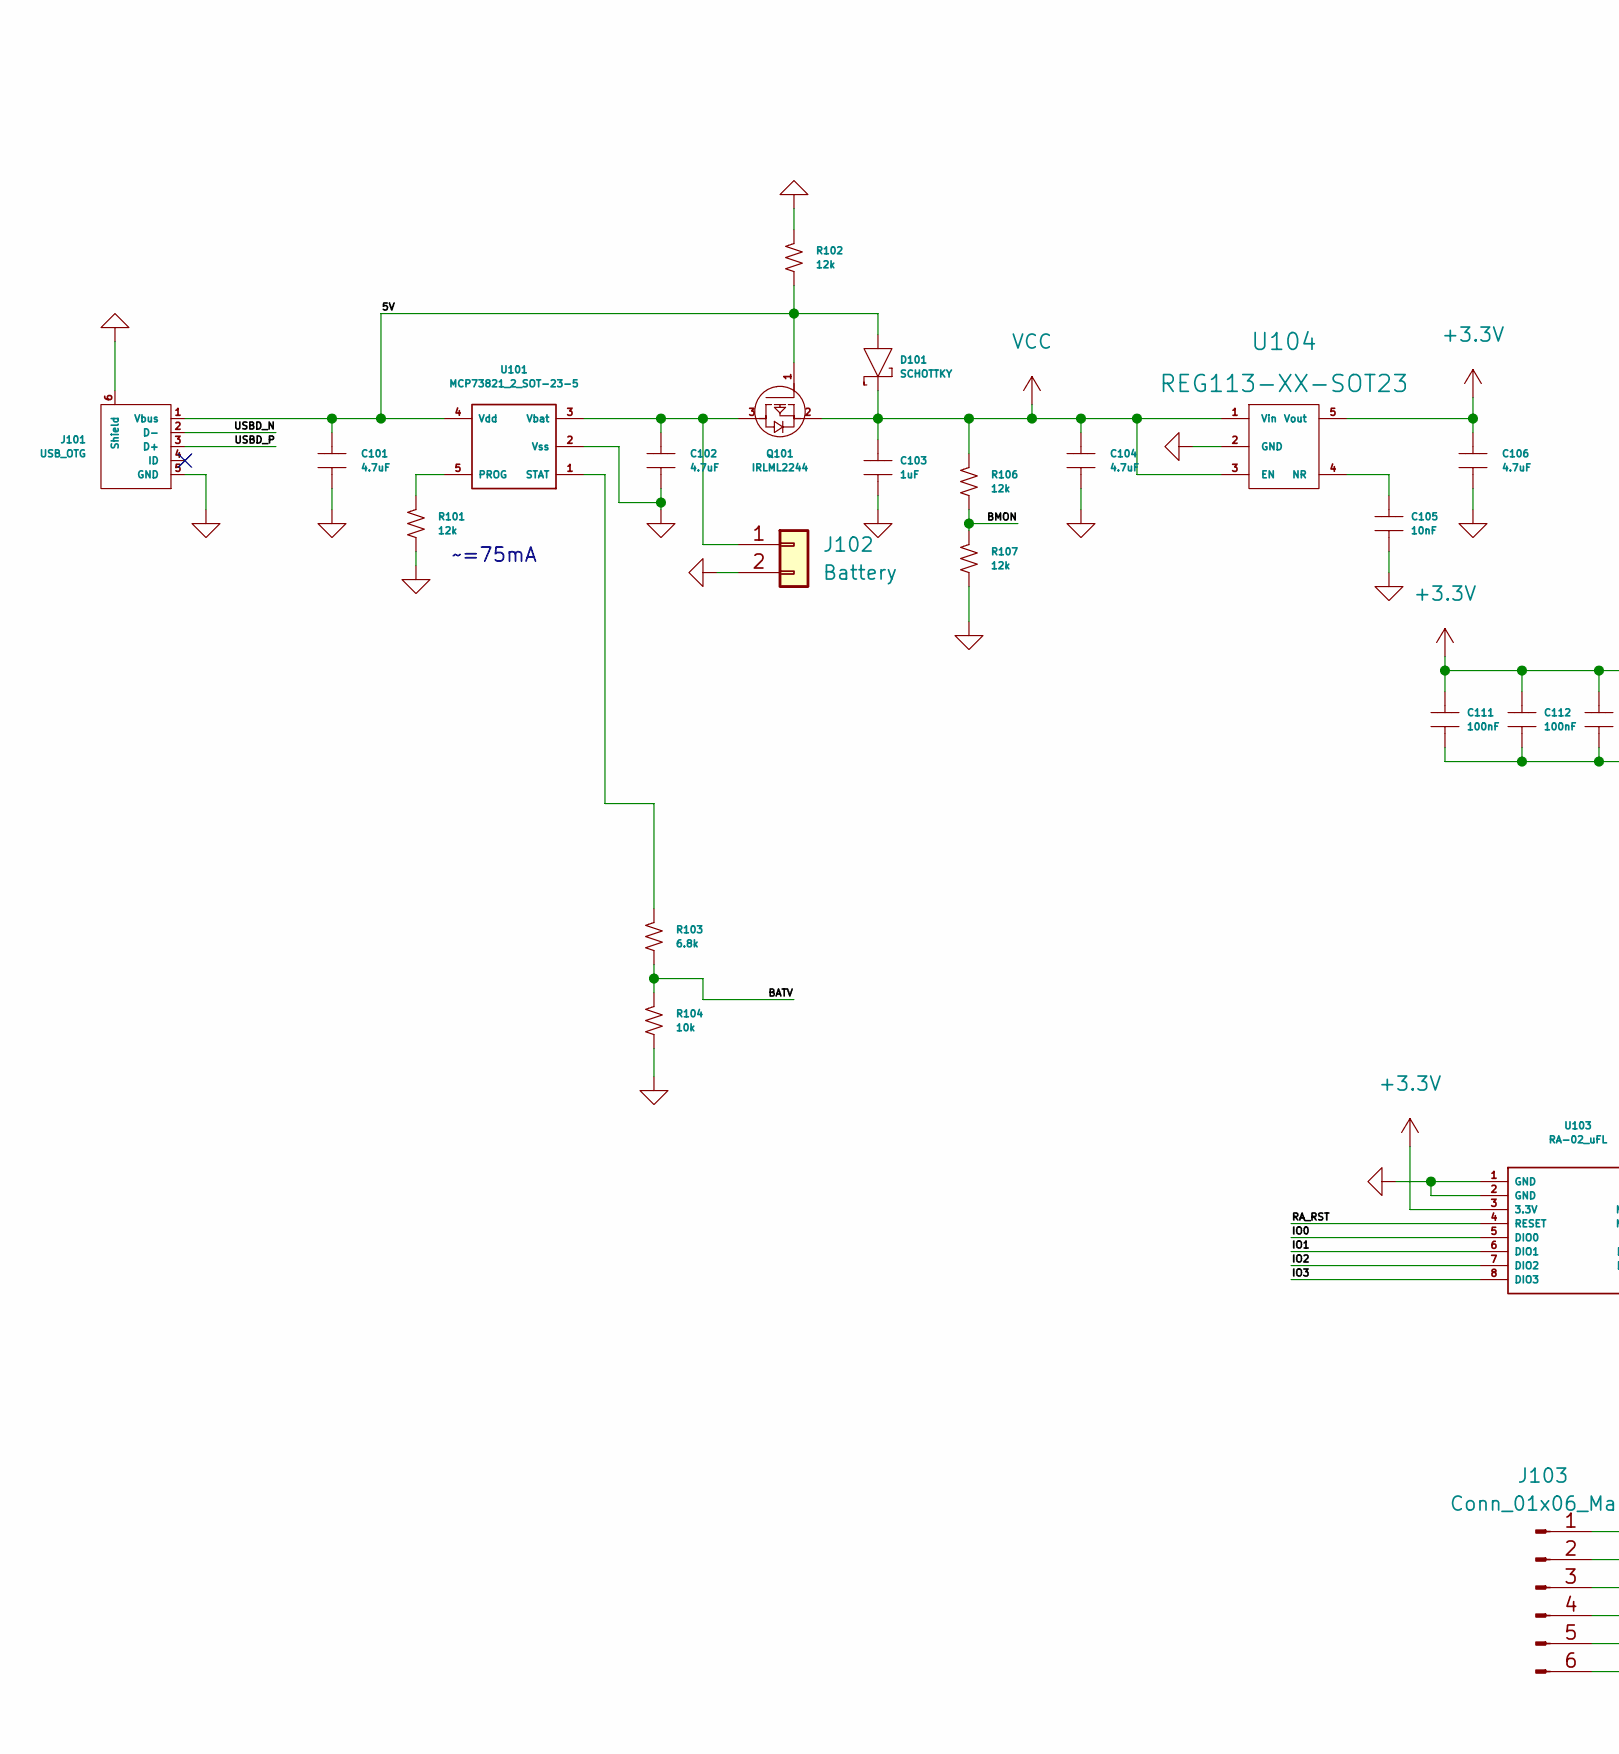
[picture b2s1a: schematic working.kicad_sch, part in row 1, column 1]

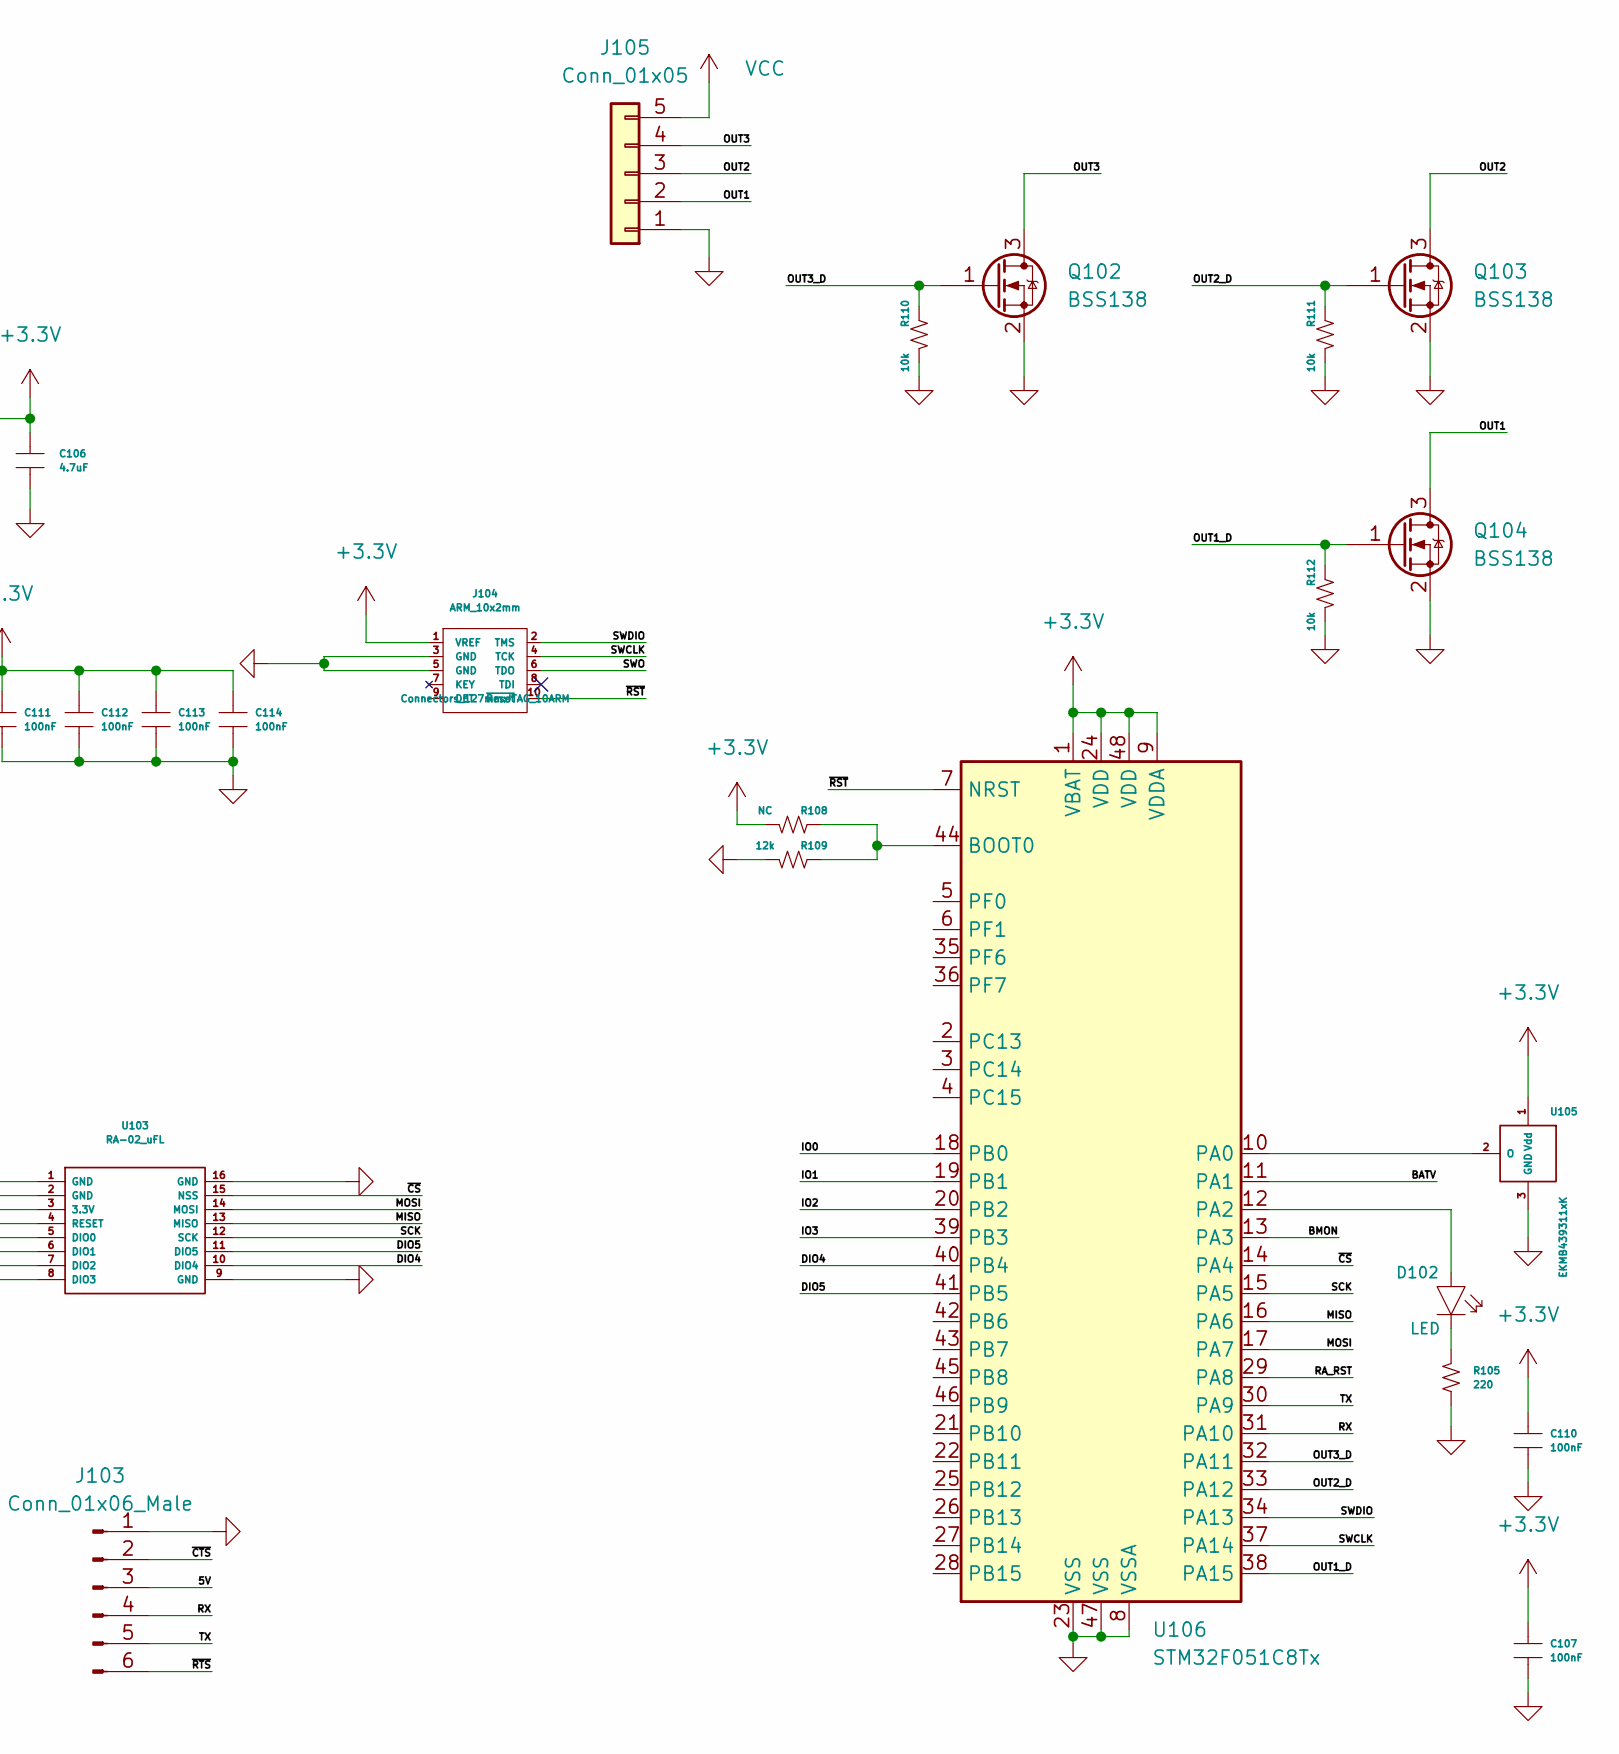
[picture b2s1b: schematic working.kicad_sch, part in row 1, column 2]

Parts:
C101, C102, C104, C106: 4.7uF; SM0805
C103: 1uF; SM0603
C105: 10nF; SM0603
C107, C110, C111, C112, C113, C114: 100nF; SM0603
D101: SCHOTTKY; SOD-123
D102: LED; LED-0805
J101: USB_OTG; USB_Micro-B_Wuerth_629105150521_CircularHoles
J102: Battery; JST_XH_B2B-XH-A_1x02_P2.50mm_Vertical
J103: Conn_01x06_Male; pin_array_6x1
J104: ARM_10x2mm; JTAG_10ARM
J105: Conn_01x05; JST_XH_B5B-XH-A_1x05_P2.50mm_Vertical
Q101: IRLML2244; SOT-23
Q102, Q103, Q104: BSS138; SOT-23
R101, R102, R106, R107, R109: 12k; SM0603
R103: 6.8k; SM0603
R104, R110, R111, R112: 10k; SM0603
R105: 220; SM0603
R108: NC; SM0603
U101: MCP73821_2_SOT-23-5; SOT23-5
U103: RA-02_uFL; RA-02_Lora
U104: REG113-XX-SOT23; SOT23-5
U105: EKMB439311xK
U106: STM32F051C8Tx; LQFP-48_7x7mm_P0.5mm

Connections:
+3V3: C106.2, C107.2, C110.2, C111.2, C112.2, C113.2, C114.2, J104.1 (VREF), R108.2, U103.3 (3.3V), U104.5 (Vout), U105.1 (Vdd), U106.1 (VBAT), U106.9 (VDDA), U106.24 (VDD), U106.48 (VDD)
/5V: C101.2, D101.A, J101.1 (Vbus), J103.3, Q101.1 (G), R102.1, U101.4 (Vdd)
/BATV: R103.1, R104.2, U106.11 (PA1)
/BMON: R106.1, R107.2, U106.13 (PA3)
/DIO4: U103.10 (DIO4), U106.40 (PB4)
/DIO5: U103.11 (DIO5), U106.41 (PB5)
/IO0: U103.5 (DIO0), U106.18 (PB0)
/IO1: U103.6 (DIO1), U106.19 (PB1)
/IO2: U103.7 (DIO2), U106.20 (PB2)
/IO3: U103.8 (DIO3), U106.39 (PB3)
/MISO: U103.13 (MISO), U106.16 (PA6)
/MOSI: U103.14 (MOSI), U106.17 (PA7)
/OUT1: J105.2, Q104.3 (D)
/OUT1_D: Q104.1 (G), R112.1, U106.38 (PA15)
/OUT2: J105.3, Q103.3 (D)
/OUT2_D: Q103.1 (G), R111.1, U106.33 (PA12)
/OUT3: J105.4, Q102.3 (D)
/OUT3_D: Q102.1 (G), R110.1, U106.32 (PA11)
/RA_RST: U103.4 (RESET), U106.29 (PA8)
/RX: J103.4, U106.31 (PA10)
/SCK: U103.12 (SCK), U106.15 (PA5)
/SWCLK: J104.4 (TCK), U106.37 (PA14)
/SWDIO: J104.2 (TMS), U106.34 (PA13)
/SWO: J104.6 (TDO)
/TX: J103.5, U106.30 (PA9)
/USBD_N: J101.2 (D-)
/USBD_P: J101.3 (D+)
/~CS: U103.15 (NSS), U106.14 (PA4)
/~CTS: J103.2
/~RST: J104.10 (~Reset), U106.7 (NRST)
/~RTS: J103.6
GND: C101.1, C102.1, C103.1, C104.1, C105.1, C106.1, C107.1, C110.1, C111.1, C112.1, C113.1, C114.1, J101.5 (GND), J101.6 (Shield), J102.2, J103.1, J104.3 (GND), J104.5 (GND), J105.1, Q102.2 (S), Q103.2 (S), Q104.2 (S), R101.1, R102.2, R104.1, R105.1, R107.1, R109.2, R110.2, R111.2, R112.2, U101.2 (Vss), U103.1 (GND), U103.2 (GND), U103.9 (GND), U103.16 (GND), U104.2 (GND), U105.3 (GND), U106.8 (VSSA), U106.23 (VSS), U106.47 (VSS)
unnamed: C102.2, J102.1, Q101.3 (D), U101.3 (Vbat)
unnamed: C105.2, U104.4 (NR)
unnamed: D102.K, R105.2
unnamed: R101.2, U101.5 (PROG)
unnamed: R103.2, U101.1 (STAT)
unnamed: U105.2 (O), U106.10 (PA0)
unnamed: D102.A, U106.12 (PA2)
unnamed: R108.1, R109.1, U106.44 (BOOT0)
VCC: C103.2, C104.2, D101.K, J105.5, Q101.2 (S), R106.2, U104.1 (Vin), U104.3 (EN)

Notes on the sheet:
~=75mA

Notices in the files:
projects/naturesyouth_ujtag/version_current/working/working.kicad_pcb:
CC BY-SA 3.0
projects/naturesyouth_ujtag/version_current/working/working.kicad_sch:
Jorge Aparicio (C) 2012
Licensed under
Creative Commons Attribution-ShareAlike 3.0 Unported
